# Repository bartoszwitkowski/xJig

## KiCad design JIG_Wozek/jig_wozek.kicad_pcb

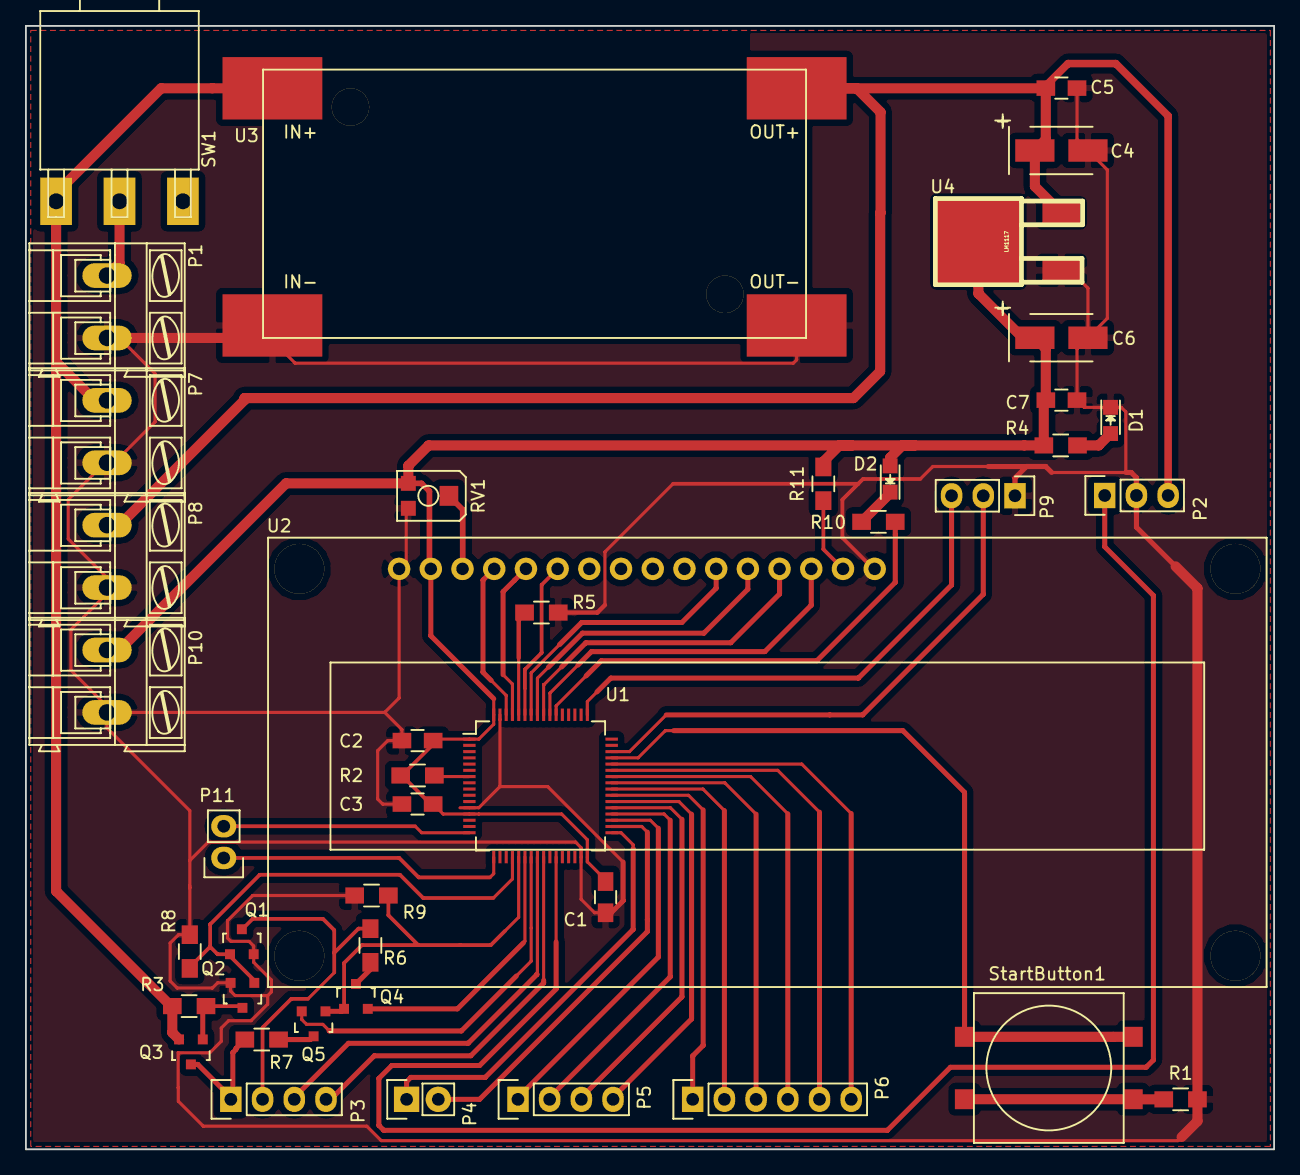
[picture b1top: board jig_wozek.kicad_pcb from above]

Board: 2 copper layers, 100.0 x 90.0 mm, 43 parts (0 on the bottom side), 49 nets.

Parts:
C1, C2, C3, C5, C7: 100nF; C_0805_HandSoldering
C4, C6: 47uF 10V; TantalC_SizeB_EIA-3528_HandSoldering
D1, D2: LED; LED_0805
P1, P7, P8, P10: CONN_01X02; AK300-2
P2: SWD; Pin_Header_Straight_1x03
P3: WTYK_A; Pin_Header_Straight_1x04
P4: HARTING_BACK; Pin_Header_Straight_1x02
P5: WTYK_B; Pin_Header_Straight_1x04
P6: HARTING_FRONT; Pin_Header_Straight_1x06
P9: Servo; Pin_Header_Straight_1x03
P11: UART; Pin_Header_Straight_1x02
Q1, Q2, Q4, Q5: IRLML6344TRPBF; SOT-23
Q3: IRLML9301TRPBF; SOT-23
R1, R4, R11: 330R; R_0805_HandSoldering
R2, R3, R5: 10k; R_0805_HandSoldering
R6, R7: 1R; R_0805_HandSoldering
R8, R9: 4k7; R_0805_HandSoldering
R10: 270R; R_0805_HandSoldering
RV1: POT; POT_SMD_3x3_5
SW1: SWITCH_INV; SW_SPDT
StartButton1: DTSM-25N-V-B; PushButton_12x12
U1: STM32F030R8T6; LQFP-64_10x10mm_Pitch0.5mm
U2: HD44780; HD44780_2x16
U3: LM2596; LM2596S-Module
U4: LM1117; LM1117_TO-252

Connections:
+3V3: C1.1, C2.1, C3.1, C6.1, C7.1, D2.2, P10.1, R2.1, R4.1, R11.2, RV1.1, U1.1, U1.13, U1.32, U1.64, U2.2, U4.2
+5V: C4.1, C5.1, P8.1, P9.3, U3.3, U4.1
+24V: P7.1, Q3.2, R3.2, SW1.1, U3.1
/3V3_BACK: P5.1, U1.35
/3V3_FRONT: P6.1, U1.39
/FAN_24V_A: P3.4, U1.25
/FAN_24V_BACK: P4.1, U1.33
/FAN_24V_FRONT: P6.3, U1.41
/FAN_GND_A: P3.3, U1.24
/FAN_GND_BACK: P4.2, U1.34
/FAN_GND_FRONT: P6.4, U1.42
/KEY_TRANSISTOR_24V: Q1.1, Q2.1, R8.1, U1.20
/KEY_TRANSISTOR_SC: Q4.1, Q5.1, R9.1, U1.21
/LCD_D4: U1.58, U2.11
/LCD_D5: U1.57, U2.12
/LCD_D6: U1.56, U2.13
/LCD_D7: U1.55, U2.14
/LCD_E: U1.59, U2.6
/LCD_RS: U1.62, U2.4
/LCD_RW: U1.61, U2.5
/LED_24V: Q5.2, U1.23
/LED_GND: Q4.2, U1.22
/RFU_BACK_1: P5.3, U1.37
/RFU_BACK_2: P5.4, U1.38
/RFU_FRONT_1: P6.6, U1.44
/RFU_FRONT_2: P6.5, U1.43
/SWCLK: P2.3, U1.49
/SWDIO: P2.2, U1.46
/TOUCHPROBE_BACK: P5.2, U1.36
/TOUCHPROBE_FRONT: P6.2, U1.40
GND: C1.2, C2.2, C3.2, C4.2, C5.2, C6.2, C7.2, D1.1, P1.2, P2.1, P7.2, P8.2, P9.2, P10.2, Q1.2, Q2.2, R1.2, R5.1, R8.2, R9.2, RV1.3, U1.12, U1.31, U1.63, U2.1, U2.16, U3.2, U4.3
unnamed: D1.2, R4.2
unnamed: D2.1, R10.1
unnamed: P1.1, SW1.2
unnamed: P3.1, Q3.3, R7.2
unnamed: P3.2, Q1.3, R6.1
unnamed: P9.1, U1.27
unnamed: P11.1, U1.17
unnamed: P11.2, U1.16
unnamed: Q2.3, Q3.1, R3.1
unnamed: Q4.3, R6.2
unnamed: Q5.3, R7.1
unnamed: R1.1, StartButton1.1
unnamed: R2.2, U1.7
unnamed: R5.2, U1.60
unnamed: R10.2, U1.54
unnamed: R11.1, U2.15
unnamed: RV1.2, U2.3
unnamed: StartButton1.2, U1.45

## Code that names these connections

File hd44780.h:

 //******************************************************************************
//    THE SOFTWARE INCLUDED IN THIS FILE IS FOR GUIDANCE ONLY.
//    AUTHOR SHALL NOT BE HELD LIABLE FOR ANY DIRECT, INDIRECT
//    OR CONSEQUENTIAL DAMAGES WITH RESPECT TO ANY CLAIMS ARISING
//    FROM USE OF THIS SOFTWARE.
//
//    PROGRAM ZAWARTY W TYM PLIKU PRZEZNACZONY JEST WYLACZNIE
//    DO CELOW SZKOLENIOWYCH. AUTOR NIE PONOSI ODPOWIEDZIALNOSCI
//    ZA ZADNE EWENTUALNE, BEZPOSREDNIE I POSREDNIE SZKODY
//    WYNIKLE Z JEGO WYKORZYSTANIA.
//******************************************************************************

//##############################################################################
// lcd_hd44780.h
// Dopasowane do zestawu uruchomieniowego STM32F0DISCOVERY by Mesho
//
// Zajrzyj na: atmegan.blogspot.com
//##############################################################################

#include <stm32f0xx_gpio.h>
#include <stm32f0xx_rcc.h>

//**********  Ustawienia pin�w wyswietlacza     **********//
#define LCD_GPIO GPIOB //port
#define LCD_CLK_LINE RCC_AHBPeriph_GPIOB //linia zegarowa, zmienic litere portu

#define LCD_D4 GPIO_Pin_6
#define LCD_D5 GPIO_Pin_5
#define LCD_D6 GPIO_Pin_4
#define LCD_D7 GPIO_Pin_3

#define LCD_RS GPIO_Pin_9
#define LCD_RW GPIO_Pin_8
#define LCD_EN GPIO_Pin_7
//********** Koniec ustawien pin�w wyswietlacza **********//


#define HD44780_CLEAR                    0x01

#define HD44780_HOME                     0x02

#define HD44780_ENTRY_MODE               0x04
#define HD44780_EM_SHIFT_CURSOR          0
#define HD44780_EM_SHIFT_DISPLAY         1
#define HD44780_EM_DECREMENT             0
#define HD44780_EM_INCREMENT             2

#define HD44780_DISPLAY_ONOFF            0x08
#define HD44780_DISPLAY_OFF              0
#define HD44780_DISPLAY_ON               4
#define HD44780_CURSOR_OFF               0
#define HD44780_CURSOR_ON                2
#define HD44780_CURSOR_NOBLINK     		 0
#define HD44780_CURSOR_BLINK           	 1

#define HD44780_DISPLAY_CURSOR_SHIFT 	 0x10
#define HD44780_SHIFT_CURSOR             0
#define HD44780_SHIFT_DISPLAY            8
#define HD44780_SHIFT_LEFT               0
#define HD44780_SHIFT_RIGHT              4

#define HD44780_FUNCTION_SET       		 0x20
#define HD44780_FONT5x7                  0
#define HD44780_FONT5x10                 4
#define HD44780_ONE_LINE                 0
#define HD44780_TWO_LINE                 8
#define HD44780_4_BIT                    0
#define HD44780_8_BIT                    16

#define HD44780_CGRAM_SET                0x40

#define HD44780_DDRAM_SET                0x80

//############# Komendy uzywane w glownym programie #############
void LCDInit(void);
void LCDClear(void);
void LCDOutString(unsigned char * text);
void LCDXY(unsigned char x, unsigned char y);
void LCDOutInt(int n);
void LCDOutuint32(uint32_t u, uint8_t n);
void LCDOutint32(int32_t u, uint8_t n);
void LCDOutuint16(uint16_t u, uint8_t n);
void LCDOutint16(int16_t u, uint8_t n);
void LCDOutuint8(uint8_t u, uint8_t n);
void LCDOutint8(int8_t u, uint8_t n);
void LCDOutFloat(float f, uint8_t calk, uint8_t ulamk);
void LCDOutUFloat(float f, uint8_t calk, uint8_t ulamk);
void LCDOutDouble(double d, uint8_t calk, uint8_t ulamk);

//###############################################################

void LCDSendByte(unsigned char dataToWrite);
void LCDAddress(unsigned char commandToWrite);
void lcd_addchar (unsigned char chrNum, unsigned char n, const unsigned char *p);

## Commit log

2016-08-31 added ewryfink
2016-08-31 checking connections finished
2016-08-31 fixed return values
2016-09-01 added error reports
2016-09-01 Added delay
2016-09-09 some changes
2016-09-11 assdfsa
2016-09-11 Added schematics
2016-09-16 asdasdljkasda
2016-09-17 safagsdfA
